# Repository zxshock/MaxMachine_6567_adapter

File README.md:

Original development by vossi: http://lc64.blogspot.com/2016/08/max6566-replacement-pcb-finshed.html
Prototyped in 2016

Documentation is "okayish". Uploaded completely "as is", since I lost all interest in the Commodore community.
Uploaded for your personal enjoyment. If I see this advertised as "r@r3 l@@k - high quality Repro of a long lost expansion!!!!!!11one" for 50€+ on eBay I sincerely hope you're getting the customers you deserve :)
The same circuit/blank PCB is also available with a different layout for a fair price at "Retro Innovations" / "go4retro"

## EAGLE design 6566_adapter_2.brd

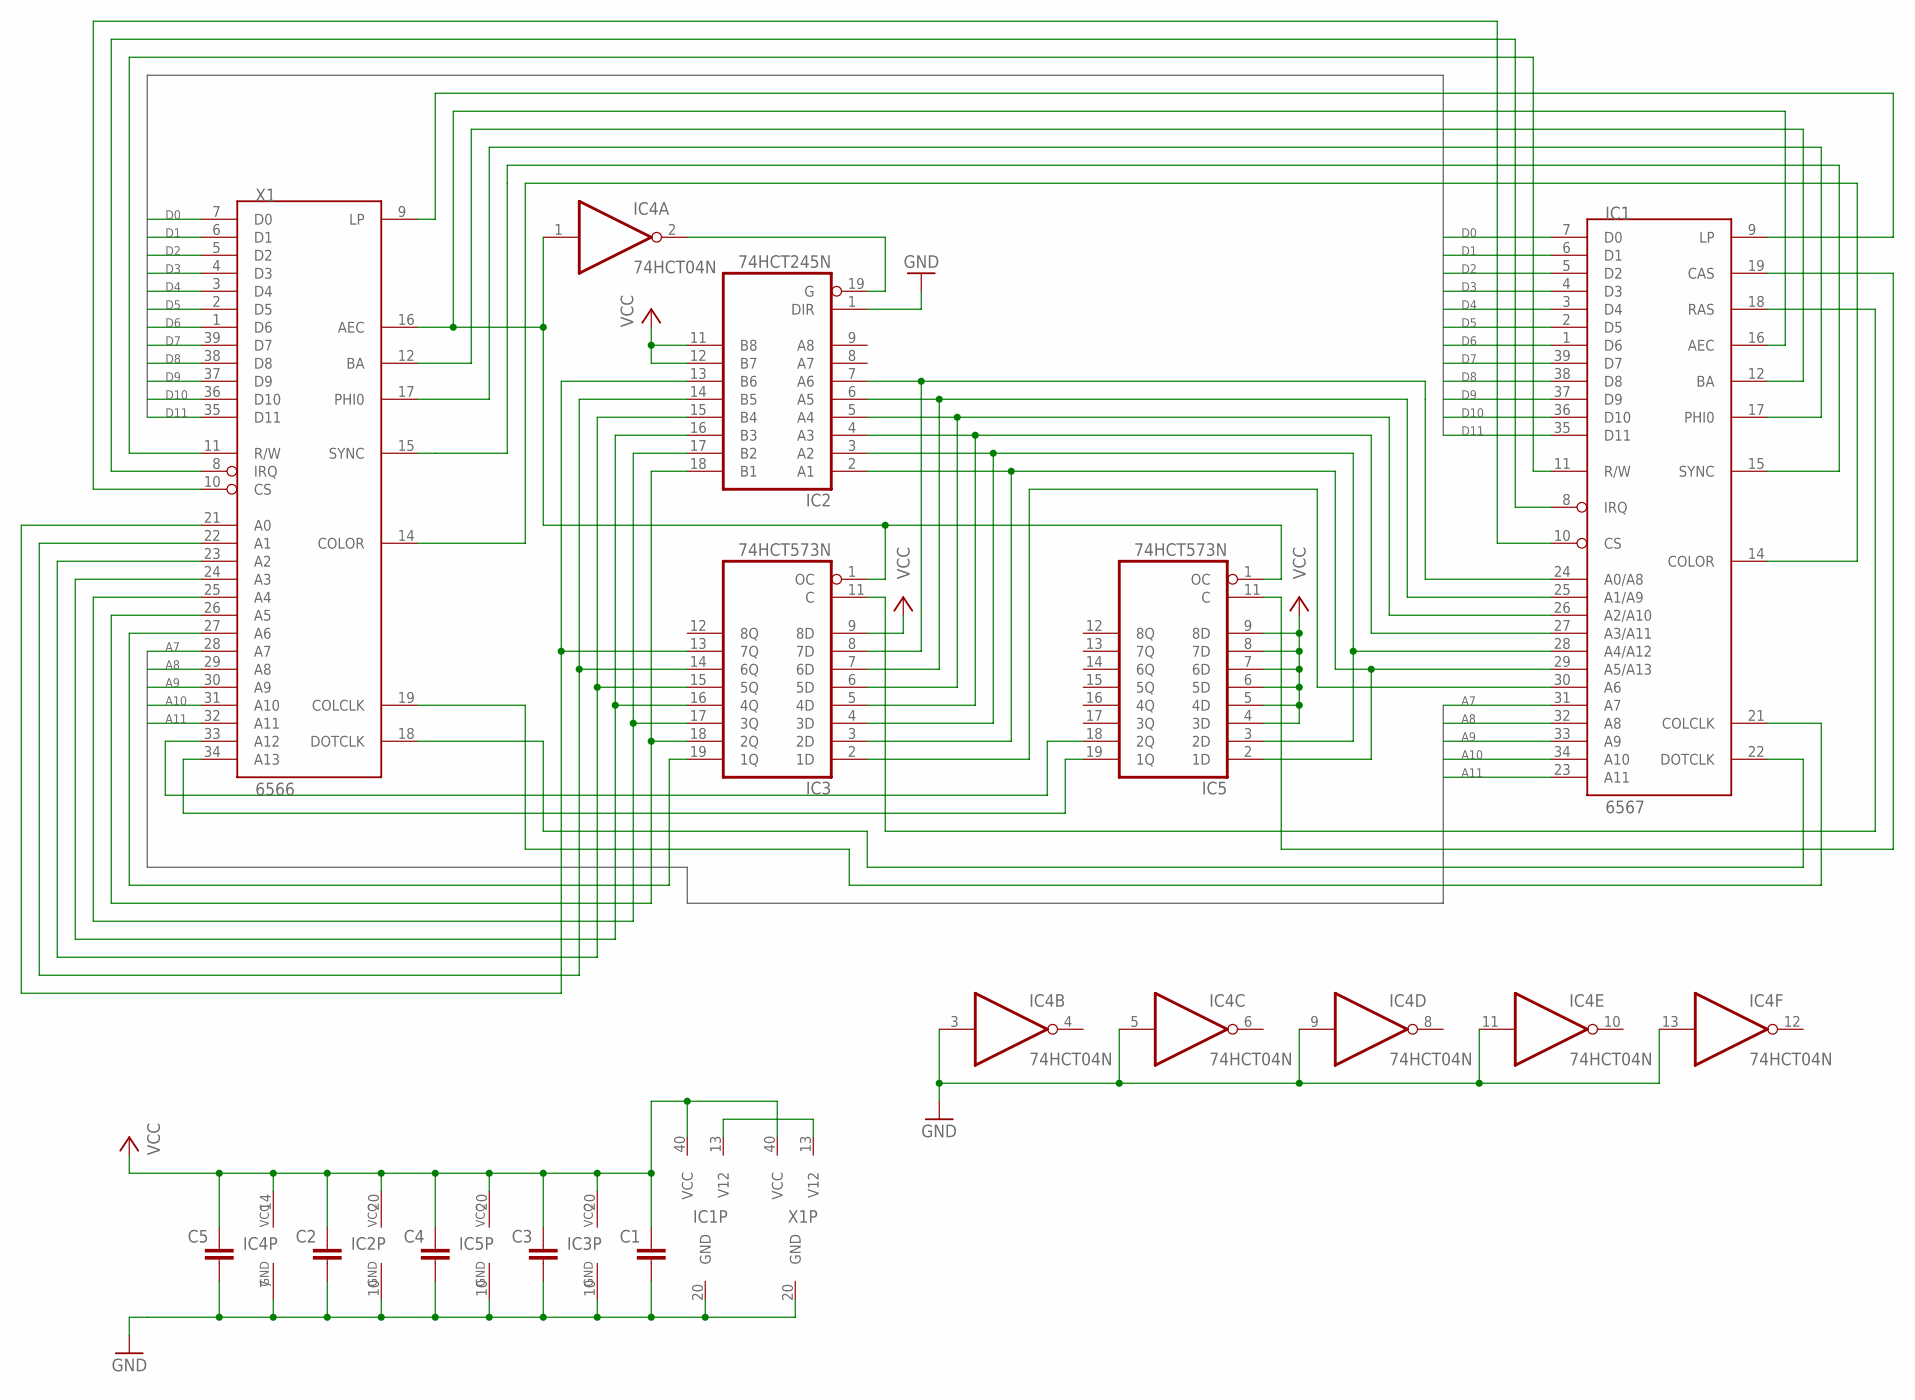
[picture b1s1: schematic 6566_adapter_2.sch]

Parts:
C1, C2, C3, C4, C5: C-EU025-025X050; C025-025X050
IC1: 6567; DIP40
IC2: 74HCT245N; DIL20
IC3, IC5: 74HCT573N; DIL20
IC4: 74HCT04N; DIL14
X1: 6566; DIL40

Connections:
!AEC: IC2.19 (G), IC4.2 (O)
!CS: IC1.10 (CS), X1.10 (CS)
!IRQ: IC1.8 (IRQ), X1.8 (IRQ)
A0: IC2.13 (B6), IC3.13 (7Q), X1.21 (A0)
A0_6567: IC1.24 (A0/A8), IC2.7 (A6), IC3.8 (7D)
A1: IC2.14 (B5), IC3.14 (6Q), X1.22 (A1)
A1_6567: IC1.25 (A1/A9), IC2.6 (A5), IC3.7 (6D)
A2: IC2.15 (B4), IC3.15 (5Q), X1.23 (A2)
A2_6567: IC1.26 (A2/A10), IC2.5 (A4), IC3.6 (5D)
A3: IC2.16 (B3), IC3.16 (4Q), X1.24 (A3)
A3_6567: IC1.27 (A3/A11), IC2.4 (A3), IC3.5 (4D)
A4: IC2.17 (B2), IC3.17 (3Q), X1.25 (A4)
A4_6567: IC1.28 (A4/A12), IC2.3 (A2), IC3.4 (3D), IC5.3 (2D)
A5: IC2.18 (B1), IC3.18 (2Q), X1.26 (A5)
A5_6567: IC1.29 (A5/A13), IC2.2 (A1), IC3.3 (2D), IC5.2 (1D)
A6: IC3.19 (1Q), X1.27 (A6)
A6_6567: IC1.30 (A6), IC3.2 (1D)
A7: IC1.31 (A7), X1.28 (A7)
A8: IC1.32 (A8), X1.29 (A8)
A9: IC1.33 (A9), X1.30 (A9)
A10: IC1.34 (A10), X1.31 (A10)
A11: IC1.23 (A11), X1.32 (A11)
A12: IC5.18 (2Q), X1.33 (A12)
A13: IC5.19 (1Q), X1.34 (A13)
AEC: IC1.16 (AEC), IC3.1 (OC), IC4.1 (I), IC5.1 (OC), X1.16 (AEC)
BA: IC1.12 (BA), X1.12 (BA)
CAS: IC1.19 (CAS), IC5.11 (C)
COLCLK: IC1.21 (COLCLK), X1.19 (COLCLK)
COLOR: IC1.14 (COLOR), X1.14 (COLOR)
D0: IC1.7 (D0), X1.7 (D0)
D1: IC1.6 (D1), X1.6 (D1)
D2: IC1.5 (D2), X1.5 (D2)
D3: IC1.4 (D3), X1.4 (D3)
D4: IC1.3 (D4), X1.3 (D4)
D5: IC1.2 (D5), X1.2 (D5)
D6: IC1.1 (D6), X1.1 (D6)
D7: IC1.39 (D7), X1.39 (D7)
D8: IC1.38 (D8), X1.38 (D8)
D9: IC1.37 (D9), X1.37 (D9)
D10: IC1.36 (D10), X1.36 (D10)
D11: IC1.35 (D11), X1.35 (D11)
DOTCLK: IC1.22 (DOTCLK), X1.18 (DOTCLK)
GND: C1.2, C2.2, C3.2, C4.2, C5.2, IC1.20 (GND), IC2.1 (DIR), IC2.10 (GND), IC3.10 (GND), IC4.3 (I), IC4.5 (I), IC4.7 (GND), IC4.9 (I), IC4.11 (I), IC4.13 (I), IC5.10 (GND), X1.20 (GND)
LP: IC1.9 (LP), X1.9 (LP)
PHI0: IC1.17 (PHI0), X1.17 (PHI0)
R/W: IC1.11 (R/W), X1.11 (R/W)
RAS: IC1.18 (RAS), IC3.11 (C)
SYNC: IC1.15 (SYNC), X1.15 (SYNC)
V12: IC1.13 (V12), X1.13 (V12)
VCC: C1.1, C2.1, C3.1, C4.1, C5.1, IC1.40 (VCC), IC2.11 (B8), IC2.12 (B7), IC2.20 (VCC), IC3.9 (8D), IC3.20 (VCC), IC4.14 (VCC), IC5.4 (3D), IC5.5 (4D), IC5.6 (5D), IC5.7 (6D), IC5.8 (7D), IC5.9 (8D), IC5.20 (VCC), X1.40 (VCC)

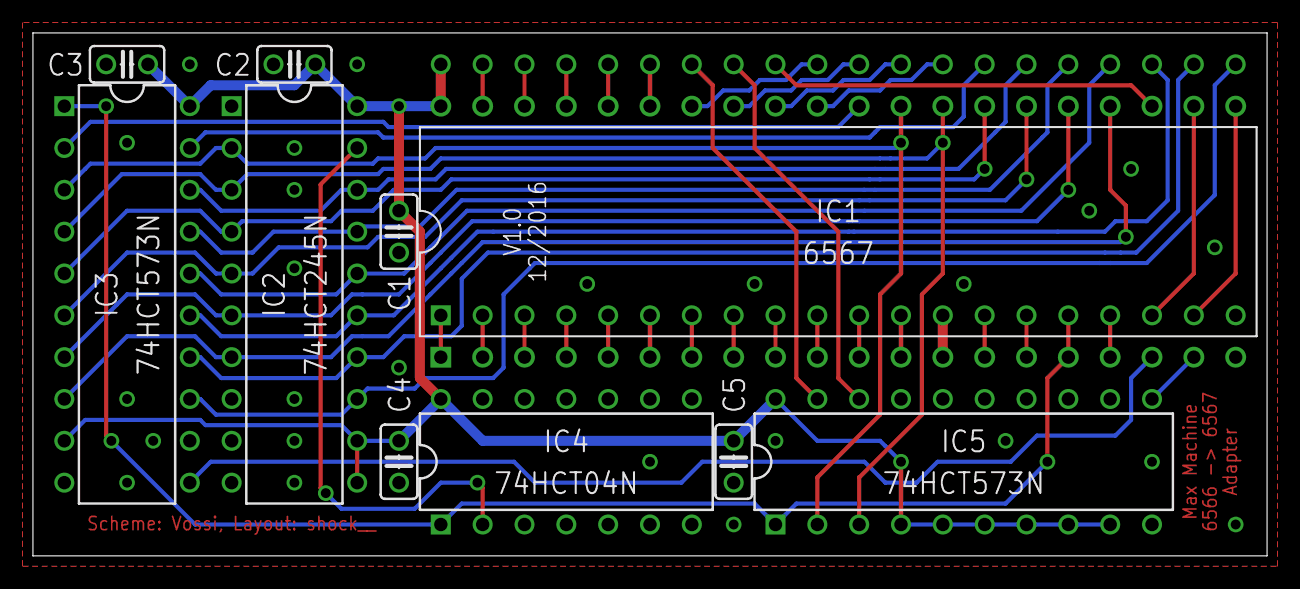
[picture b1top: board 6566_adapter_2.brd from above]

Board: 2 copper layers, 74.9 x 31.8 mm, 11 parts (0 on the bottom side), 50 nets.
